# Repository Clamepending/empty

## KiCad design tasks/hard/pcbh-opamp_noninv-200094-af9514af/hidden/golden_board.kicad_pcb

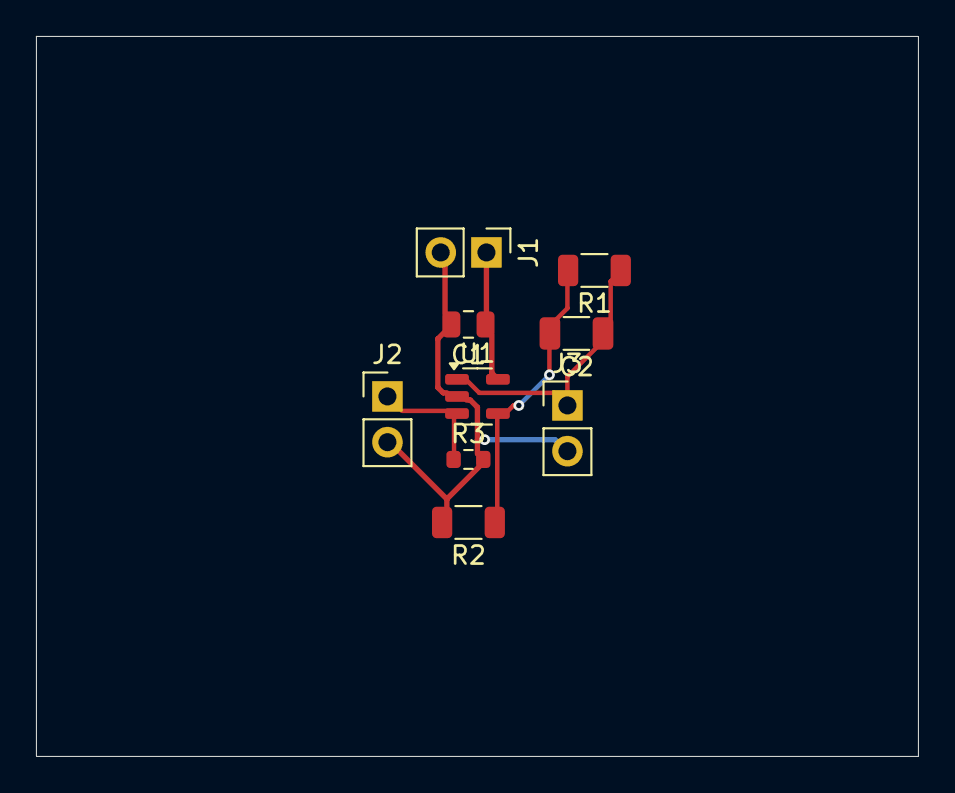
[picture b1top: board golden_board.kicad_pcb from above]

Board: 2 copper layers, 49.0 x 40.0 mm, 9 parts (0 on the bottom side), 5 nets.

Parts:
C1: 100n; C_0805_2012Metric
C2: 470p; C_1206_3216Metric
J1, J2, J3: PinHeader_1x02_P2.54mm_Vertical
R1: 12.7k; R_1206_3216Metric
R2: 1.82k; R_1206_3216Metric
R3: 470k; R_0603_1608Metric
U1: SOT-23-5

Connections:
FB: C2.2, R1.2, R2.1, U1.4
GND: C1.2, J1.2, J2.2, J3.2, R2.2, R3.2, U1.2
IN: J2.1, R3.1, U1.3
OUT: C2.1, J3.1, R1.1, U1.1
VCC: C1.1, J1.1, U1.5

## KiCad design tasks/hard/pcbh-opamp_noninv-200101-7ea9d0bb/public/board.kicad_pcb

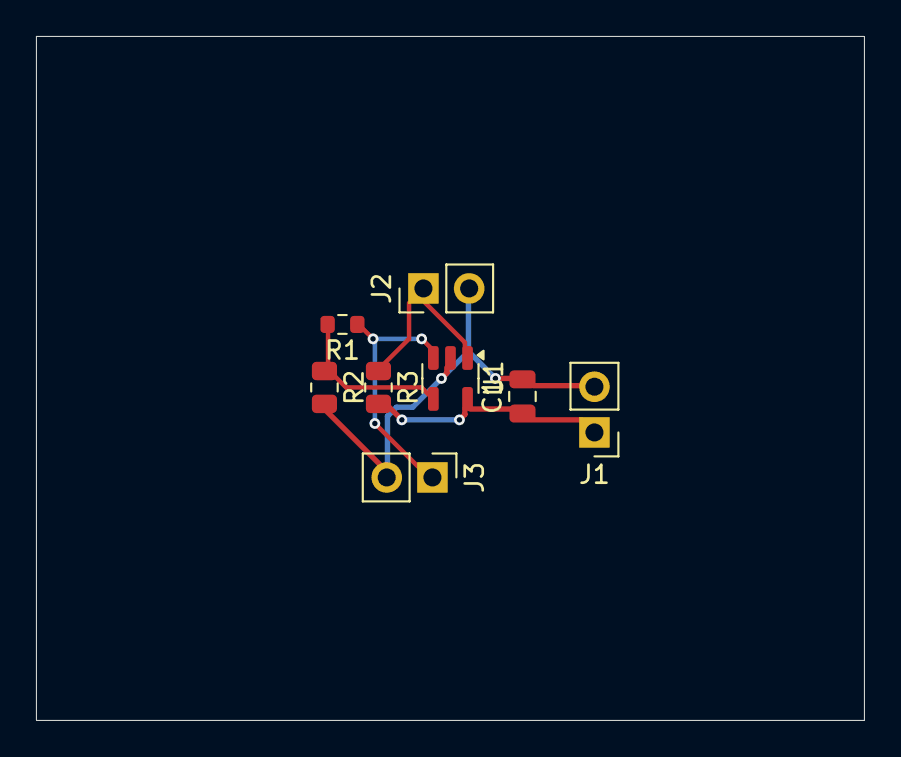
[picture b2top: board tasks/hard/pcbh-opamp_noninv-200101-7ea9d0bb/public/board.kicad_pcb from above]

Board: 2 copper layers, 46.0 x 38.0 mm, 8 parts (0 on the bottom side), 5 nets.

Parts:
C1: 100n; C_0805_2012Metric
J1, J2, J3: PinHeader_1x02_P2.54mm_Vertical
R1: 20.5k; R_0603_1608Metric
R2: 2.26; R_0805_2012Metric
R3: 100k; R_0805_2012Metric
U1: SOT-23-5

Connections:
FB: R1.2, R2.1, U1.4
GND: C1.2, J1.2, J2.2, J3.2, R2.2, U1.2
IN: J2.1, R3.1, U1.1
OUT: J3.1, R1.1, U1.3
VCC: C1.1, J1.1, R3.2, U1.5

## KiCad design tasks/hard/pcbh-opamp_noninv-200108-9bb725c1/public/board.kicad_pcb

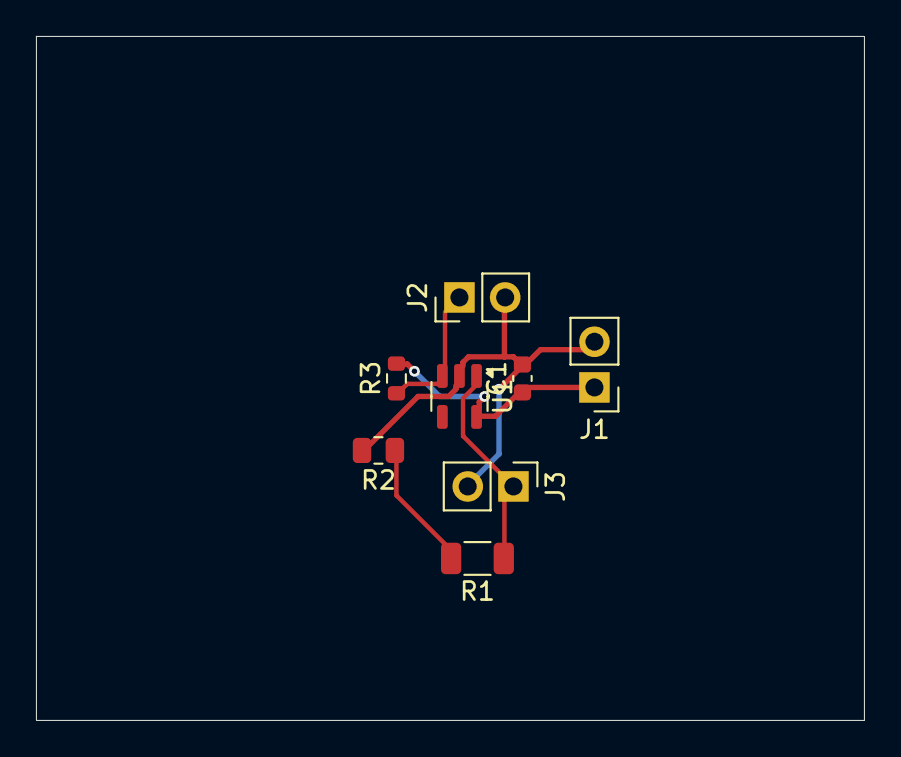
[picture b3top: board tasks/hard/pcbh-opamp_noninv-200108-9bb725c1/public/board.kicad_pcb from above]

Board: 2 copper layers, 46.0 x 38.0 mm, 8 parts (0 on the bottom side), 5 nets.

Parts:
C1: 100n; C_0603_1608Metric
J1, J2, J3: PinHeader_1x02_P2.54mm_Vertical
R1: 240k; R_1206_3216Metric
R2: 1.21k; R_0805_2012Metric
R3: 1M; R_0603_1608Metric
U1: SOT-23-5

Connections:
FB: R1.2, R2.1
GND: C1.2, J1.2, J2.2, J3.2, R2.2, U1.2
IN: J2.1, R3.1, U1.3
OUT: J3.1, R1.1, U1.1
VCC: C1.1, J1.1, R3.2, U1.5
